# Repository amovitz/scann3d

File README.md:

# scann3d

Real-time 3D object scanner using the VL53L8CX multi-zone time-of-flight sensor with dual LSM6DSVTR‎ IMU position tracking.

## Features

- **64-zone 3D visualization** - See the VL53L8CX's 8x8 measurement grid as rays in 3D space
- **Real-time IMU tracking** - Each LSM6DSVTR‎ gives independent real-time positioning
- **Temporal filtering** - Exponential moving average smooths noisy measurements
- **Plane fitting** - Least squares and RANSAC methods for surface detection
- **Mapping mode** - Accumulate points over time to build a 3D map of your environment

## Hardware

**Components (~$34/board, porotype cost as of 2026-03-18):**

- ESP32-C3-WROOM-02-N4‎ (~$3)
- VL53L8CX ToF sensor (~$7)
- 2x LSM6DSVTR‎ IMU (~$3)

All sensors share the I2C bus (same SDA/SCL pins).

### v1

Note: Distance scanning plane here appears curved, however distance reported by the VL53L8CX is perpendicular, not radial.

## Installation

### ESP32 Firmware

[Zephyr Firmware Instructions](zephyr-firmware/README.md)

### Python Viewer

**TODO:** Unbreak the integration with this Zephyr firmware...

```bash
pip install -r viewer/requirements.txt
```

## Usage

### ESP32 Board

| LED | Color | Behavior | Meaning |
|---|---|---|---|
| D1 | White | Blinking | Booting |
| D1 | Yellow | Blinking | WiFi connecting |
| D1 | Red | Blinking | WiFi disconnected |
| D1 | Green | Steady | WiFi connected |
| D1 | Green | Blinking | Output (USB serial+UDP) sending data |
| D1 | Off | Steady | Booted, actively scanning |
|---|---|---|---|
| D2 | White | Blinking | Booting |
| D2 | Cyan | Steady | Servo init failure |
| D2 | Magenta | Steady | UART0 init failure |
| D2 | Red | Steady | Output (USB serial+UDP) init failure |
| D2 | Green | Steady | ToF, IMU0 init success |
| D2 | Green | Blinking | ToF, IMU0, IMU1 init success |
| D2 | Yellow | Steady | ToF init success |
| D2 | Blue | Steady | IMU0 init success |
| D2 | Blue | Blinking | IMU0, IMU1 init success |
| D2 | Off | Steady | Booted, actively scanning |

Note: The LEDs will turn off after successfully booting and scanning begins. The ToF sensor works best in darkroom conditions.

### Python Viewer

```bash
python -m viewer --port /dev/ttyACM0
```

Open http://localhost:8080 in your browser.

**Options:**
- `--port`, `-p`: Serial port (default: `/dev/ttyACM0`)
- `--baud`, `-b`: Baud rate (default: `115200`)
- `--viser-port`: Viser server port (default: `8080`)
- `--debug`: Enable verbose logging

## Sensor Specs

**VL53L8CX** ([datasheet](https://www.st.com/resource/en/datasheet/vl53l8cx.pdf)):
- **FoV:** 65° diagonal (45° Hoizontal/Vertical)
- **Range:** 20mm - 4000mm
- **Distance type:** Perpendicular (z-axis), not radial

| Resolution | Zones | Max Frequency |
| ---------- | ----- | ------------- |
| 4x4        | 16    | 60 Hz         |
| 8x8        | 64    | 15 Hz         |

Currently configured for 8x8 at 15Hz.

---

## Forked from [ferrolho/VL53L5CX-BNO08X-viewer](https://github.com/ferrolho/VL53L5CX-BNO08X-viewer)

## License

MIT

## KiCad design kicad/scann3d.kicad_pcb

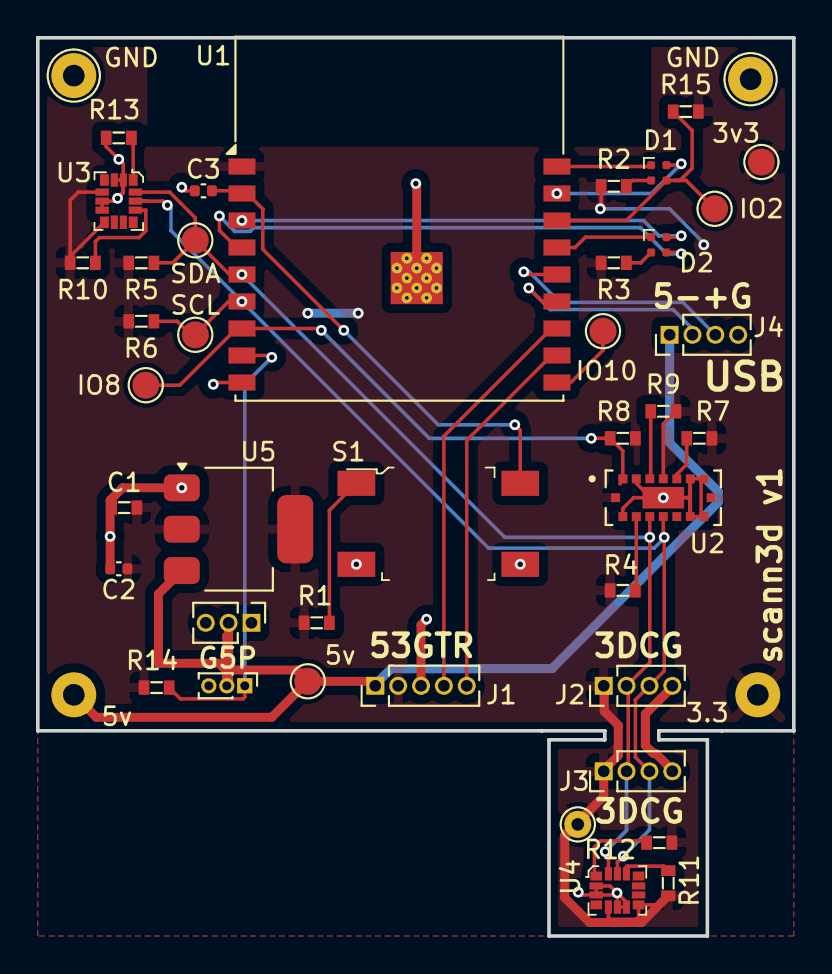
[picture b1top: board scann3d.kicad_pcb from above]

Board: 2 copper layers, 42.0 x 49.9 mm, 40 parts (0 on the bottom side), 26 nets.

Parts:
3v3: LDO_Out; TestPoint_Pad_D1.5mm
5v: LDO_In; TestPoint_Pad_D1.5mm
C1: 100nf; 0603 (3D)
C2: 4.7uf; C_0402_1005Metric (3D)
C3: 100nf; C_0402_1005Metric (3D)
D1, D2: UHD111A-FKA; LED_Lumex_SML-LX0404SIUPGUSB
GND: TestPoint_THTPad_D2.5mm_Drill1.2mm
GND#2: TestPoint_THTPad_D2.5mm_Drill1.2mm
IO2: IO2; TestPoint_Pad_D1.5mm
IO8, IO10: LDO_In; TestPoint_Pad_D1.5mm
J1: Conn_01x05_Pin; PinHeader_1x05_P1.27mm_Vertical
J2, J3, J4: EXT_I2C; PinHeader_1x04_P1.27mm_Vertical
M1: 2589; PinHeader_1x03_P1.00mm_Vertical
R1, R14: 100k; 0603 (3D)
R2, R3, R15: 10k; 0603 (3D)
R4, R7, R8, R9, R10, R11, R12, R13: 47k; 0603 (3D)
R5, R6: 2.2k; 0603 (3D)
S1: 1825910-6; Switch_Tactile_SMD_6x6mm
SCL: SCL; TestPoint_Pad_D1.5mm
SDA: SDA; TestPoint_Pad_D1.5mm
U1: ESP32-C3-WROOM-02
U2: VL53L5CXV0GC_1; XDCR_VL53L5CXV0GC_1
U3, U4: LSM6DS3TR; LGA-14L_2.5x3mm__LSM6DS3
U5: LM3480-3.3; SOT-223-3_TabPin2

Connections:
+3.3V: 3v3.1, C1.1, C2.1, J1.2, J2.1, J3.1, R1.2, R2.2, R3.2, R4.1, R5.1, R6.1, R7.2, R8.2, R9.1, R10.2, R11.2, R12.1, R14.2, R15.1, U1.1 (3V3), U2.A4 (IOVDD), U2.B1 (AVDD), U2.B7 (AVDD__1), U3.5 (VDDIO), U3.8 (VDD), U4.5 (VDDIO), U4.8 (VDD), U5.2 (VO)
+5V: 5v.1, J1.1, J4.1, M1.2 (+), U5.3 (VI)
/I2C_RST: IO8.1, R8.1, U1.7 (IO8), U2.A1 (I2C_RST)
/PWM: M1.1 (PWM), R14.1, U1.8 (IO9)
/RXD: J1.5, U1.11 (IO20/RXD)
/SCL: J2.3, J3.3, R6.2, SCL.1, U1.6 (IO7), U2.C4 (SCL), U3.13 (SCL), U4.13 (SCL)
/SDA: J2.2, J3.2, R5.2, SDA.1, U1.5 (IO6), U2.C3 (SDA), U3.14 (SDA), U4.14 (SDA)
/TXD: J1.4, U1.12 (IO21/TXD)
GND: C1.2, C2.2, C3.2, GND.2, GND#2.1, J1.3, J2.4, J3.4, J4.4, M1.3 (-), R13.1, S1.3, S1.4, U1.9 (GND), U1.19 (GND), U2.A2 (RSVD4), U2.A6 (RSVD1), U2.A7 (RSVD2), U2.B4 (THERMALPAD), U2.C1 (GND), U2.C6 (RSVD3), U2.C7 (GND__1), U3.2 (SDx), U3.3 (SCx), U3.6 (GND), U3.7 (GND), U4.2 (SDx), U4.3 (SCx), U4.6 (GND), U4.7 (GND), U5.1 (GND)
unnamed: D1.4 (A), R2.1
unnamed: D1.1 (BK), U1.18 (IO0)
unnamed: D1.2 (GK), U1.17 (IO1)
unnamed: D1.3 (RK), IO2.1, R15.2, U1.16 (IO2)
unnamed: D2.4 (A), R3.1
unnamed: D2.1 (BK), U1.15 (IO3)
unnamed: D2.2 (GK), U1.3 (IO4)
unnamed: D2.3 (RK), U1.4 (IO5)
unnamed: R1.1, S1.1
unnamed: C3.1, S1.2, U1.2 (EN)
unnamed: R9.2, U2.A3 (INT)
unnamed: R7.1, U2.A5 (LPN)
unnamed: R4.2, U2.C2 (RSVD6)
unnamed: R10.1, U3.12 (CS)
unnamed: R13.2, U3.1 (SDO/SA0)
unnamed: R11.1, U4.12 (CS)
unnamed: R12.2, U4.1 (SDO/SA0)

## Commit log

2026-03-22 Moves old firmware into an archive directory.
2026-03-22 Adds scann3d v1 hardware.
2026-03-22 Initial zephyr yolo commit.
    This zephyr project was templated by claude.ai (Sonnet 4.6, Extended)
    given the sensors and pinout. No shot it works lmao
2026-03-22 Adds new assets and documentation.
2026-03-22 Fixes issues with VL53L8CX ULD.
    Adds instructions to download and set up VL53L8CX ULD drivers.
2026-03-22 Fixes USB serial output.
    Data is written out to the USB serial console as well as being directed
    to UDP output.
2026-03-22 Fixes wifi_mgr.c compilation errors.
    The entire project now builds.
2026-03-22 Fixes warnings and using the correct base devkit DTS.
2026-03-22 Formats comments and removes special symbols.
2026-03-22 More documentation fixes...
2026-03-22 Cleans up LED control and documents indicator behavior.
2026-03-22 Prints more network info.
2026-03-22 Adds a link to the VL53L8CX ULD reference manual.
2026-03-22 Adds a JSON serializer.
2026-03-22 Adds servo position reporting.
2026-03-22 Adds TODO.
2026-03-23 Splits jobs into a separate work queue source files.
    Should make testing and modification easier.
2026-03-26 Minor reorder.
2026-03-26 Adds a zephyr-ide.json config for VSCode.
2026-03-26 Turns off LEDs when scanning has started.
2026-03-28 Adds esptool as an automatic pip install.
